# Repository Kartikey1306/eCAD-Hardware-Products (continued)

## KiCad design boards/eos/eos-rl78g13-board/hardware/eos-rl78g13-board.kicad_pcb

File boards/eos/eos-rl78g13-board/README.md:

# EoS RL78G13 Board

An original R5F100LEAFB RL78/G13 development board, 30 × 100 mm, two layers, with two
30-pin expansion headers, a USB-C serial port and an external TOOL0 debug connector.
Designed by Kartikeydheer Srivastava.
All rights reserved: not open source, and not under this repository's MIT licence.
Anyone may view it, clone this repository and run its tests; anything more needs
Kartikeydheer Srivastava's written permission (kartikeydheer@gmail.com). EmbeddedOS (EoS) Research Foundation has a limited, revocable
permission. See [LICENSE.txt](LICENSE.txt) and [the licence summary](../README.md#licence).

A board for the same job as the Renesas YRPBRL78G13; an original design, not a copy:
no design file of the vendor's was used; the header positions come from the 25.4 mm
separation and 30 × 100 mm envelope dimension callouts in
[Renesas R01UH0243ED0000 Rev.1.0, page 70](https://www.renesas.com/en/document/mah/rl78g13-stick-yrpbrl78g13),
with the 2.54 mm pitch and pin functions from pages 18–20. The undimensioned distance
along the board is an original choice: both pin-1 centres are 2.54 mm from the bottom edge.
No schematic, copper layout, Gerber or BOM from that board was used. Mechanical drop-in
compatibility is unverified. This board uses 3.3 V I/O; VDD is not the reference board's 5 V.

| | |
|---|---|
|  |  |

## What is on it

| Block | Parts, settings and source |
|---|---|
| MCU | Renesas [R5F100LEAFB#10](https://www.renesas.com/en/products/rl78-g13/part-details/r5f100leafb-10), LFQFP-64, 64 KB code flash, 4 KB data flash, 4 KB RAM. Internal high-speed oscillator supports 32 MHz at this supply; select HS flash mode in firmware. [R01DS0131EJ0380](https://www.renesas.com/en/document/dst/rl78g13-data-sheet), §§1.1–1.3.11 and electrical characteristics. |
| MCU supply | VDD and EVDD0 share the nominal 3.283 V rail; VSS and EVSS0 share ground. Each supply has 100 nF; REGC has a specified 680 nF, 35 V, ±10% X7R 0805 capacitor to ground (C3; see capacitance budget below). Unused X1/X2 inputs have individual 10 kΩ pull-downs. [R01UH0146EJ0380](https://www.renesas.com/en/document/man/rl78g13-users-manual-hardware), §2.2, Table 2-3 and §23.1. |
| RTC subclock | NDK NX3215SA-32.768K-STD-MUA-14, 32.768 kHz, CL = 6 pF, ESR ≤70 kΩ, with two 7 pF C0G loads. This combination appears in the RL78 hardware manual's §5.7 resonator table (R01UH0146EJ0380, Resonator and Oscillator Constants). [NDK NX3215SA](https://www.ndk.com/images/products/catalog/c_NX3215SA_e.pdf). Start with normal oscillation mode; measure frequency and startup on hardware before using a lower-power setting. |
| USB-C | HRO TYPE-C-31-M-12, 5.1 kΩ on each CC pin ([USB Type-C specification](https://www.usb.org/usb-type-cr-cable-and-connector-specification), Rd), SP0503BAHTG common-anode TVS on D+, D− and VBUS. There are no data-line steering diodes to VBUS. USB layout and bridge values follow [CP2102N Rev.1.5, §§2.1–2.3](https://www.silabs.com/documents/public/data-sheets/cp2102n-datasheet.pdf). |
| Supply | Littelfuse 1206L050YR 500 mA fuse, Nexperia PMEG6010CEH Schottky, TPS7A9101DSKR LDO. 3.57 kΩ / 1.15 kΩ, both 0.1%, set 3.283 V; 10 µF input, 10 µF output, 10 nF NR/SS. [TI TPS7A91 SBVS282A](https://www.ti.com/lit/ds/symlink/tps7a91.pdf), Table 7-1 and §7.1.3. |
| USB UART | CP2102N-A02-GQFN24R: TXD → P14/RxD2, RXD ← P13/TxD2. VIO, VDD and VREGIN share the board supply, each with 4.7 µF and 100 nF bypass. RSTb has 1 kΩ pull-up. VBUS sense uses 22.1 kΩ / 47.5 kΩ, plus 1.5 kΩ VBUS bleed. CP2102N Rev.1.5 Figs.2.3/2.5. |
| Debug | Unshrouded, unkeyed 2×7, 2.54 mm connector with the Renesas E1/E2/E2 Lite TOOL0 pinout (see the keying warning below); 1 kΩ TOOL0 pull-up, a reset-choice jumper (Fig.2-10) and a 10 kΩ RESET pull-up (Fig.2-11 asks 1–10 kΩ where RESET_OUT alone drives RESET). [R20UT1994, Table 2-2 and Figs.2-5, 2-10 and 2-11](https://www.renesas.com/en/document/mat/e1e20e2-emulator-e2-emulator-lite-additional-document-users-manual-notes-connection-rl78). |
| User I/O | Reset switch, P137/INTP0 user switch with 10 kΩ pull-up, red P17 LED with 750 Ω and yellow P16 LED with 680 Ω. Both LEDs are active high and share their expansion pins. [Kingbright red](https://www.kingbrightusa.com/images/catalog/SPEC/APTD1608LSURCK.pdf), [yellow](https://www.kingbrightusa.com/images/catalog/SPEC/APTD1608LSYCK.pdf) and [green power LED](https://www.kingbrightusa.com/images/catalog/SPEC/APTD1608LCGCK.pdf) specify typical VF at 2 mA. |

C3 is **Murata GCM21BR7YA684KA55L**, 680 nF, 35 V, ±10%, X7R, 0805.
The RL78 hardware manual §23.1/Table 23-1 requires 0.47–1 µF on REGC, whose
operating voltage is 1.8 or 2.1 V. [Murata electrical characteristic data](https://ds.murata.com/simserve/characteristics?ReqType=TechPDF&partnumber=GCM21BR7YA684KA55&lang=en&techpdfname=technical_pdf_Capacitor01)
and [SimSurfing](https://ds.murata.com/simsurfing/mlcc.html?partnumbers=%5B%22GCM21BR7YA684KA55%22%5D)
provide the part's bias and temperature models. A model sweep at 0.01 Vrms, −40 to
+85 °C in 5 °C steps, and 0–3.325 V gave 0.652–0.691 µF; DC-bias change relative
to zero bias stayed within ±0.74%. With the full ±10% tolerance and ±15% X7R
limits, a separate 3% bias/AC allowance and 5% aging reserve give a calculated
0.479–0.886 µF envelope. These allowances are design reserves, not manufacturer
guarantees: the models are typical. Qualify production lots and substitutions at
REGC voltage and temperature, including aging, against the 0.47–1 µF requirement.
C3 is placed next to REGC with a short ground return.

## Power and operation

Power the board through USB-C only. J1.2 and J2.2 are **3.3 V outputs**. Do not inject
power there or enable target power from an attached debug probe. The MCU and USB bridge
always share a rail, so a powered MCU cannot drive an unpowered bridge. The Schottky and
VBUS bleed also keep the sense input from reporting a host through leakage.

External loads on J1.2 and J2.2 share one **150 mA** budget. Reserve 40 mA for the board,
for a total below 190 mA. The board itself takes about 31 mA from data-sheet typical and
maximum values: MCU IDD1 ≤ 7.0 mA (R01DS0131), CP2102N 9.5 mA typical, the three LEDs
6.2 mA, the feedback divider 0.70 mA and the P137 button 0.33 mA on 3.3 V, plus the LDO's
ground current ≤ 3.5 mA and the 3.33 mA VBUS bleed on 5 V. **With an E1, E2 or E2 Lite
fitted**, the probe draws about 20 mA from VDD at 3.3 V (R20UT1994 §2.5.4) and a low TOOL0
adds 3.3 mA through R16: the board then needs about 54 mA, so keep external loads at or
below **130 mA** while a probe is connected. Before using that allowance, program the CP2102N Max Power
descriptor to 0xFA (500 mA), and let the USB host configure the device; its factory value
0x32 requests 100 mA (CP2102N Table 7.1). With the factory descriptor, or before USB
configuration, keep external loads at or below 50 mA. This is a design budget, not a
measured load limit or USB certification.

The board does not implement CP2102N SUSPEND-controlled load switching or MCU suspend
firmware. The MCU, power LED and VBUS bleed remain powered when the host suspends.
**This board does not meet the USB 2.0 suspend current limit:** the VBUS bleed alone draws
5.0 V / 1.5 kΩ = 3.33 mA, above the 2.5 mA allowed. Changing Max Power alone does not make
this a compliant high-power USB device: attach current, enumeration and attach inrush are
unverified. The 10 µF LDO
input capacitor has positive tolerance, and downstream capacitors (about 35 µF on 3.3 V,
including the 10 µF at the header supply) also charge during startup; the fuse and Schottky are not an active inrush limiter. Validate these cases
on a prototype and add load/inrush control before claiming USB power compliance.

At 190 mA, a 4.75 V source, fuse R1max = 0.70 Ω, and conservative diode drop 0.53 V leave
at least 4.087 V at the LDO. Its specified maximum dropout is 0.20 V at 1 A. Ignoring the
upstream drops, worst-case dissipation is approximately `(5.25 − 3.283) × 0.190 = 0.374 W`.
The LDO's 62.5 °C/W JEDEC figure predicts about 24 °C rise; the thermal resistance of this
two-layer board has not been measured. Verify temperature and supply droop on a prototype.
The fuse's 0.42 A hold rating at 40 °C exceeds this budget. See the
[Littelfuse 1206L product data](https://www.littelfuse.com/~/media/files/littelfuse/technical%20resources/documents/product%20catalogs/littelfuse_polyfuse_pptcs.pdf)
and [Nexperia PMEG6010CEH](https://assets.nexperia.com/documents/data-sheet/PMEG6010CEH.pdf).

JP1 uses **one shunt**:

| Position | Operation |
|---|---|
| 1–2 | Normal run: reset switch and J2.19 connect to MCU RESET. |
| 2–3 | External probe: its RESET_OUT connects to MCU RESET; the switch and J2.19 feed the probe's RESET_IN. |

Connect the debug cable with both systems powered off, align its pin 1, select JP1 2–3,
and disable probe target power. After debugging, power off, unplug the cable and return
JP1 to 1–2. Hot plugging is unsupported because the reset capacitance used for that mode
would change the interface. R15, 10 kΩ, pulls MCU RESET up: R20UT1994 Figure 2-11 asks
for 1–10 kΩ where RESET_OUT alone drives RESET, as it does with JP1 at 2–3. It draws
0.33 mA while RESET is held low and also keeps RESET from floating while JP1 is open; it
does not replace the operating shunt. Order one 2.54 mm two-position jumper shunt with JP1.

**J4 is not keyed.** It is a plain 2×7 pin header, because a keyed 25.0 mm box header
(R20UT1994 Figure 2-4) does not fit across this board between J1 and J2. Check pin 1 every
time: it is the square pad at J4's lower left, marked "1" on the silkscreen. A cable plugged in the
wrong way round puts probe pin k on board pin 15 − k. The probe's RESET_OUT (13) then
lands on board ground (2), and its TOOL0 (5) and ground (2) both land on E2_RSTOUT (pins 10
and 13), so the probe's TOOL0 is tied to its own ground. R20UT1994 §2.2 warns that a
cable connected the wrong way may be damaged. With J1 and J2 fitted on the top side, the
free span between their 2.54 mm housings is about 22.86 mm. A 14-way IDC socket is about
22.4 mm long (distributor data for 3M 89114-0101, not a 3M drawing), about 0.2 mm clear on
each side. The fit of the E2 Lite cable's own plug has not been checked.

| J4 pin | Signal | J4 pin | Signal |
|---|---|---|---|
| 1 | NC | 2 | GND |
| 3 | NC | 4 | NC |
| 5 | TOOL0 | 6 | RESET_IN |
| 7 | NC | 8 | VDD sense |
| 9 | TOOL0 supply sense | 10 | RESET_OUT |
| 11 | NC | 12 | GND |
| 13 | RESET_OUT | 14 | GND |

USB carries UART2, not native MCU USB. Configure P13 as TxD2 and P14 as RxD2. Do not drive
P14 from expansion hardware while the bridge is fitted: it is already driven by CP2102N
TXD. P11/P12 remain expansion GPIO/UART0. The board has no COM-port programming/debug
support; use J4 for programming. Firmware must configure unused expansion GPIO inputs
with pull-ups or as safe outputs to prevent floating inputs.

## Expansion pinout

With USB at the top, J1 is the right row and J2 the left row. Both are fitted on the top
side, with the components. Pin 1 is at the bottom, marked by a square pad, and numbering
proceeds toward USB. Rows are 25.4 mm apart.
The published signal assignment is retained; VDD is 3.3 V on this design.

| Pin | J1 | J2 |
|---|---|---|
| 1 | GND | GND |
| 2 | VDD output | VDD output |
| 3 | P10 | P140 |
| 4 | P11 | P141 |
| 5 | P12 | P00 |
| 6 | P13 / UART TX | P01 |
| 7 | P14 / UART RX | P02 |
| 8 | P15 | P03 |
| 9 | P16 / yellow LED | P04 |
| 10 | P17 / red LED | P130 (output only) |
| 11 | P55 | P20 / AVREFP |
| 12 | P54 | P21 / AVREFM |
| 13 | P53 | P22 |
| 14 | P52 | P23 |
| 15 | P51 | P24 |
| 16 | P50 | P25 |
| 17 | P60 / SCLA0 | P26 |
| 18 | P61 / SDAA0 | P27 |
| 19 | P62 | User reset |
| 20 | P63 | P120 |
| 21 | P31 | P43 |
| 22 | P77 | P42 |
| 23 | P76 | P41 |
| 24 | P75 | P137 / button (input only) |
| 25 | P74 | P146 |
| 26 | P73 | P147 |
| 27 | P72 | P06 |
| 28 | P71 | P05 |
| 29 | P70 | P30 |
| 30 | NC | NC |

P60–P63 are open-drain ports; supply suitable external pull-ups when using them as outputs.
Use 3.3 V peripherals and check the MCU's pin-specific limits. P20/P21 can be ADC reference
inputs; firmware must choose the intended ADC reference before use.

## Not on this board

- The vendor's proprietary on-board debug probe, its firmware, demonstration software and
  virtual-UART implementation. Standard TOOL0 and CP2102N replace those functions.
- A 5 V MCU supply, USB Mini-B, an MCU-only current-measurement jumper or an external
  supply input. All powered logic shares the regulated rail.
- A main-clock crystal. The internal high-speed oscillator supplies the CPU clock; the
  fitted 32.768 kHz crystal supplies the subsystem clock.
- The vendor's 9 mm USB-end corner radii. The original outline retains the 30 × 100 mm
  envelope with 1 mm corners; no enclosure-fit claim is made.

## Layout

The figures below were measured on the routed board with the independent review's scripts:
copper paths run through pads, tracks, vias and both pours on a 0.05 mm grid, and the
resistances assume 35 µm copper.

**3.3 V distribution.** The LDO's output capacitor C14 is the star point. Three branches leave
it, all laid as fixed routes before the autorouter runs:
- The headers and the debug connector: 85.1 mm down the free strip outside J2 to J2.2, then
  27.0 mm along the bottom edge through their own 10 µF + 100 nF (C22, C23) to J1.2. J4's VDD
  pins and the reset/TOOL0 pull-ups join this bus.
- The CP2102N: through the feedback divider's sense end (R8) to its bypass row, 9.0 mm.
- The MCU: from the same point through R11 and a trunk inside the MCU's right pad row to C1 and
  C2, 53.5 mm to VDD.

No header current passes the MCU's or the bridge's capacitors. With the MCU cluster's copper
removed the headers stay fed, and with the header feed removed the MCU stays fed. The nearest
3.3 V copper is 1.59 mm from the crystal and its load capacitors. The tracks stay 0.30 mm wide: a wider
track cannot enter the 0.5 mm-pitch pins of U1, U3 and U4, and the board generator gives every
track of a net the same width. At 150 mA the header feed drops about 21 mV at J2.2 (0.14 Ω) and
28 mV at J1.2 (0.18 Ω).

**Sub-clock crystal.** R01UH0146EJ0380 Figure 5-13(d) forbids a power or ground pattern under
the XT1/XT2 wiring and the resonator. Pour keep-outs leave both layers bare there: on each layer
the ground pour covers 0 % of the XT-line strip (x 13.9–15.1, y 50.4–55.0 mm) and of Y1's
footprint, and no via sits under the crystal. The load capacitors' ground loop (C4 to C5) joins
the MCU's ground at C2's ground pad by one route (Figure 5-13(f)). Router keep-outs on the loop's
other three sides stop the autorouter joining any other ground to it: with that one route cut,
the loop has no copper path to ground. The MCU's VSS/EVSS0 node reaches ground through the top
pour and C2's ground via, 0.81 mm from C2's pad, without using the loop. That is its only via:
there was no clear spot for one beside C1.

**CP2102N bypass.** Each capacitor's ground reaches the bridge's ground through a via into the
solid bottom pour:

| Capacitor | Copper path to U3.2 (GND) | To U3's exposed pad | Straight line to U3.2 |
|---|---|---|---|
| C21 100 nF | 5.06 mm | 5.12 mm | 3.86 mm |
| C17 100 nF | 5.55 mm | 5.60 mm | 4.81 mm |
| C19 100 nF | 6.50 mm | 6.55 mm | 5.75 mm |
| C16 4.7 µF | 7.75 mm | 7.80 mm | 7.05 mm |
| C18 4.7 µF | 9.30 mm | 9.35 mm | 8.59 mm |
| C20 4.7 µF | 10.85 mm | 10.90 mm | 10.13 mm |

C21, C17, C18 and C20 have their own via, 0.81–0.97 mm from the ground pad. C19 and C16 reach
their neighbours' vias through short top-layer tracks: the autorouter moved the vias placed for
them. Most of each path is the straight-line distance, so only re-placing the row could bring it
under 5 mm. The row stays west of the chip because the supply pins (5–7) are at its top-left
corner, the USB lines leave its top edge and the VBUS-sense and reset lines leave its left edge.

**TOOL0.** TOOL0 runs 43.6 mm on the top layer with no via. Its only long neighbour within 1 mm
is the 3.3 V feed of its own pull-up (23.2 mm), a DC rail. RESET runs 4.4 mm beside it where both
leave the MCU's pins, a slow line; the other runs are 1.9 mm or less, at the MCU's pins and just
below JP1. It no longer runs beside P04/SCK10 (R20UT1994 §2.5.2).

**USB connector.** The ESD array's common anode (U2.1) has its own ground via 1.0 mm away. Its
copper path is 7.14 mm to the receptacle's A1 ground contact and 12.69 mm to B1. VBUS still
crosses under the A-row D+ and D− on the bottom layer at y = 8.44 mm, at right angles: joining
the receptacle's two VBUS contact groups has to cross the pair somewhere. Full-speed USB should
tolerate a short crossing; its effect has not been measured.

**LDO.** The input capacitor C13 has a ground via 1.22 mm from its ground pad, with 8.98 mm of
copper to U4's thermal pad. C15 (NR/SS) has a via 0.78 mm from its ground pad. The TPS7A91's
1.2 × 2.0 mm thermal pad has **no vias**, although TI SBVS282A §7.4.1 asks for an array of
them. The board generator puts vias only in exposed pads over 1.5 mm across, and no spot beside
U4's ground pins was clear of other copper. Its heat spreads through the top pour; the nearest
ground via is 2.63 mm from the pad's centre. Measure the regulator's temperature on a prototype
before relying on the 0.374 W case above.

## Build results

The numbers below are from `build-report.json` and `drc.json` in this folder.

| Check | Result |
|---|---|
| Schematic ERC | 0 violations |
| DRC errors | 0 |
| Unconnected items | 0 |
| Schematic ↔ board parity | 0 differences |
| DRC warnings | 2: silkscreen within the board-edge clearance, the outline of J3 (USB-C), which sits at the board edge |

## Fabrication

Two layers, 1.6 mm FR-4, ground pours on both sides. Design rules use 0.15 mm clearance,
0.15 mm default signal tracks, 0.20 mm USB tracks, 0.25 mm ground tracks, 0.30 mm
regulated-supply tracks and 0.40 mm VBUS tracks; allowed minimum track width is 0.10 mm.
VBUS narrows to 0.30 mm for its last 0.9 mm into R7's 0402 pad, and +5V to 0.225 mm for
0.41 mm at C13; both carry under 0.2 A. Standard vias are 0.60 mm
with 0.30 mm drill, with a 0.25 mm minimum drill rule. The four vias in the CP2102N's
exposed pad (U3) sit inside its paste apertures, where tenting cannot cover them: order them
**filled and capped (IPC-4761 Type VII)**, so solder does not wick down them. The board
file asks for tenting only (plugging, filling and capping are "no"), so name this in the
fabrication order. Confirm
the fabrication files and actual minimum features before ordering.

## What has not been done

- **No board has been fabricated or tested.** Digital rule checks do not establish analog,
  USB, thermal, ESD, debug or crystal performance.
- No firmware, CP2102N configuration image, USB certification or hardware debug session
  is included. The Max Power descriptor change above is a setup requirement.
- The public drawing does not dimension the longitudinal header offset. Exact mechanical
  interchangeability, enclosure fit and cable clearance are unverified.

## Rebuild

```sh
python3 tools/eos_boards/build.py eos_rl78g13_board
```

The source is [tools/eos_boards/boards/eos_rl78g13_board.py](../../../tools/eos_boards/boards/eos_rl78g13_board.py).

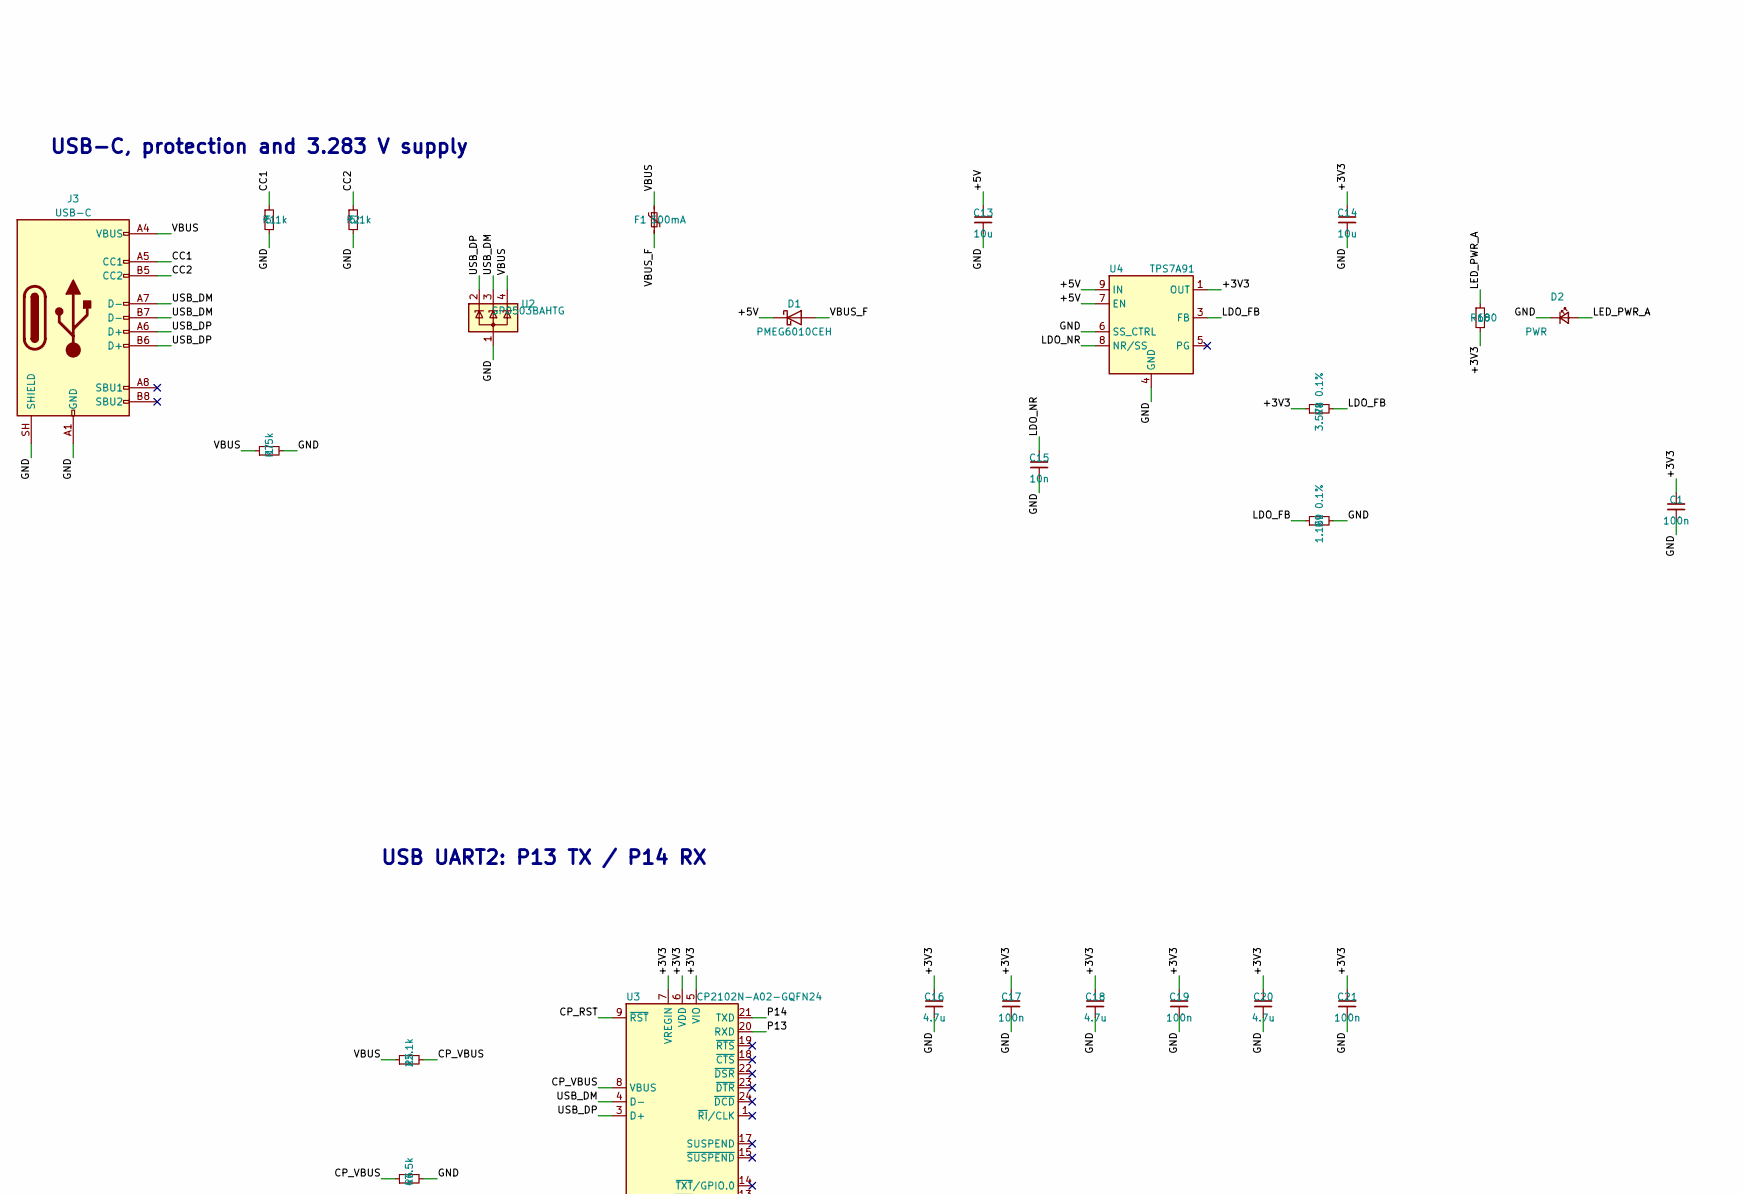
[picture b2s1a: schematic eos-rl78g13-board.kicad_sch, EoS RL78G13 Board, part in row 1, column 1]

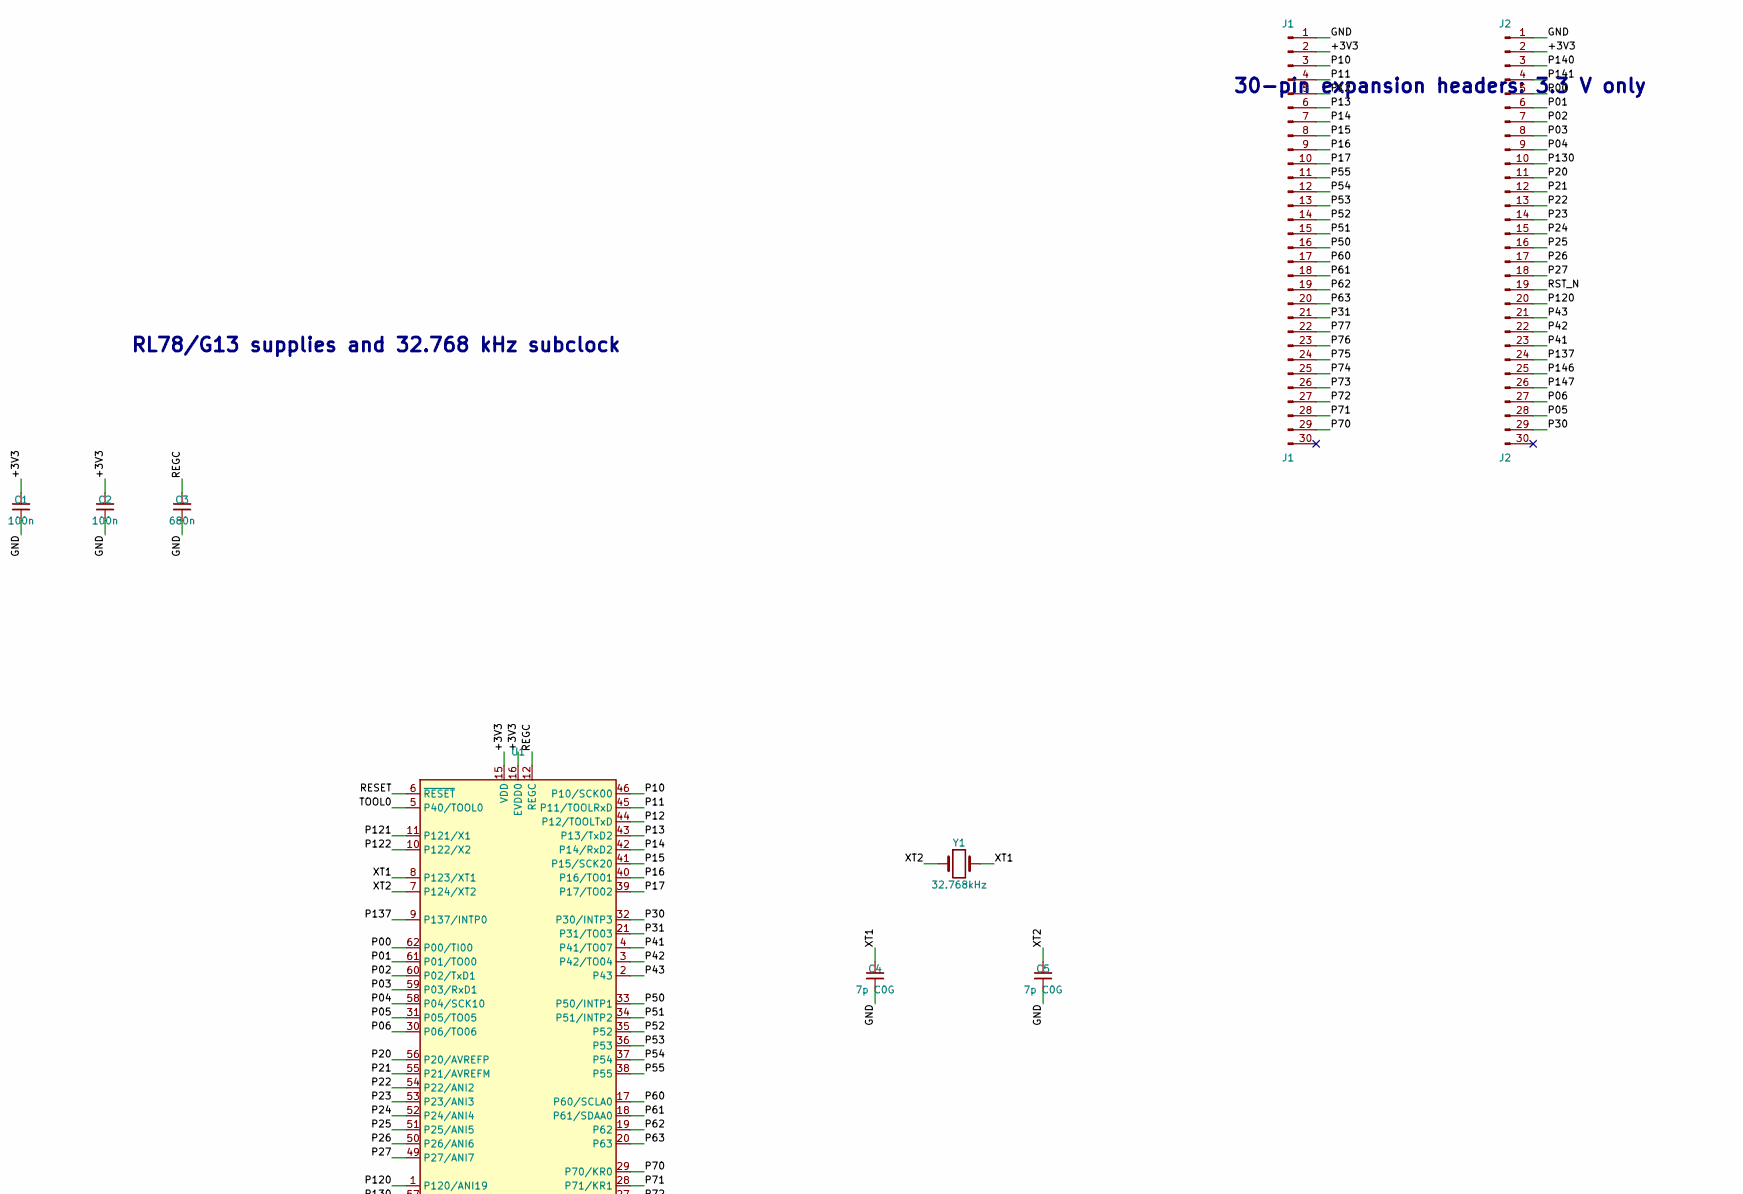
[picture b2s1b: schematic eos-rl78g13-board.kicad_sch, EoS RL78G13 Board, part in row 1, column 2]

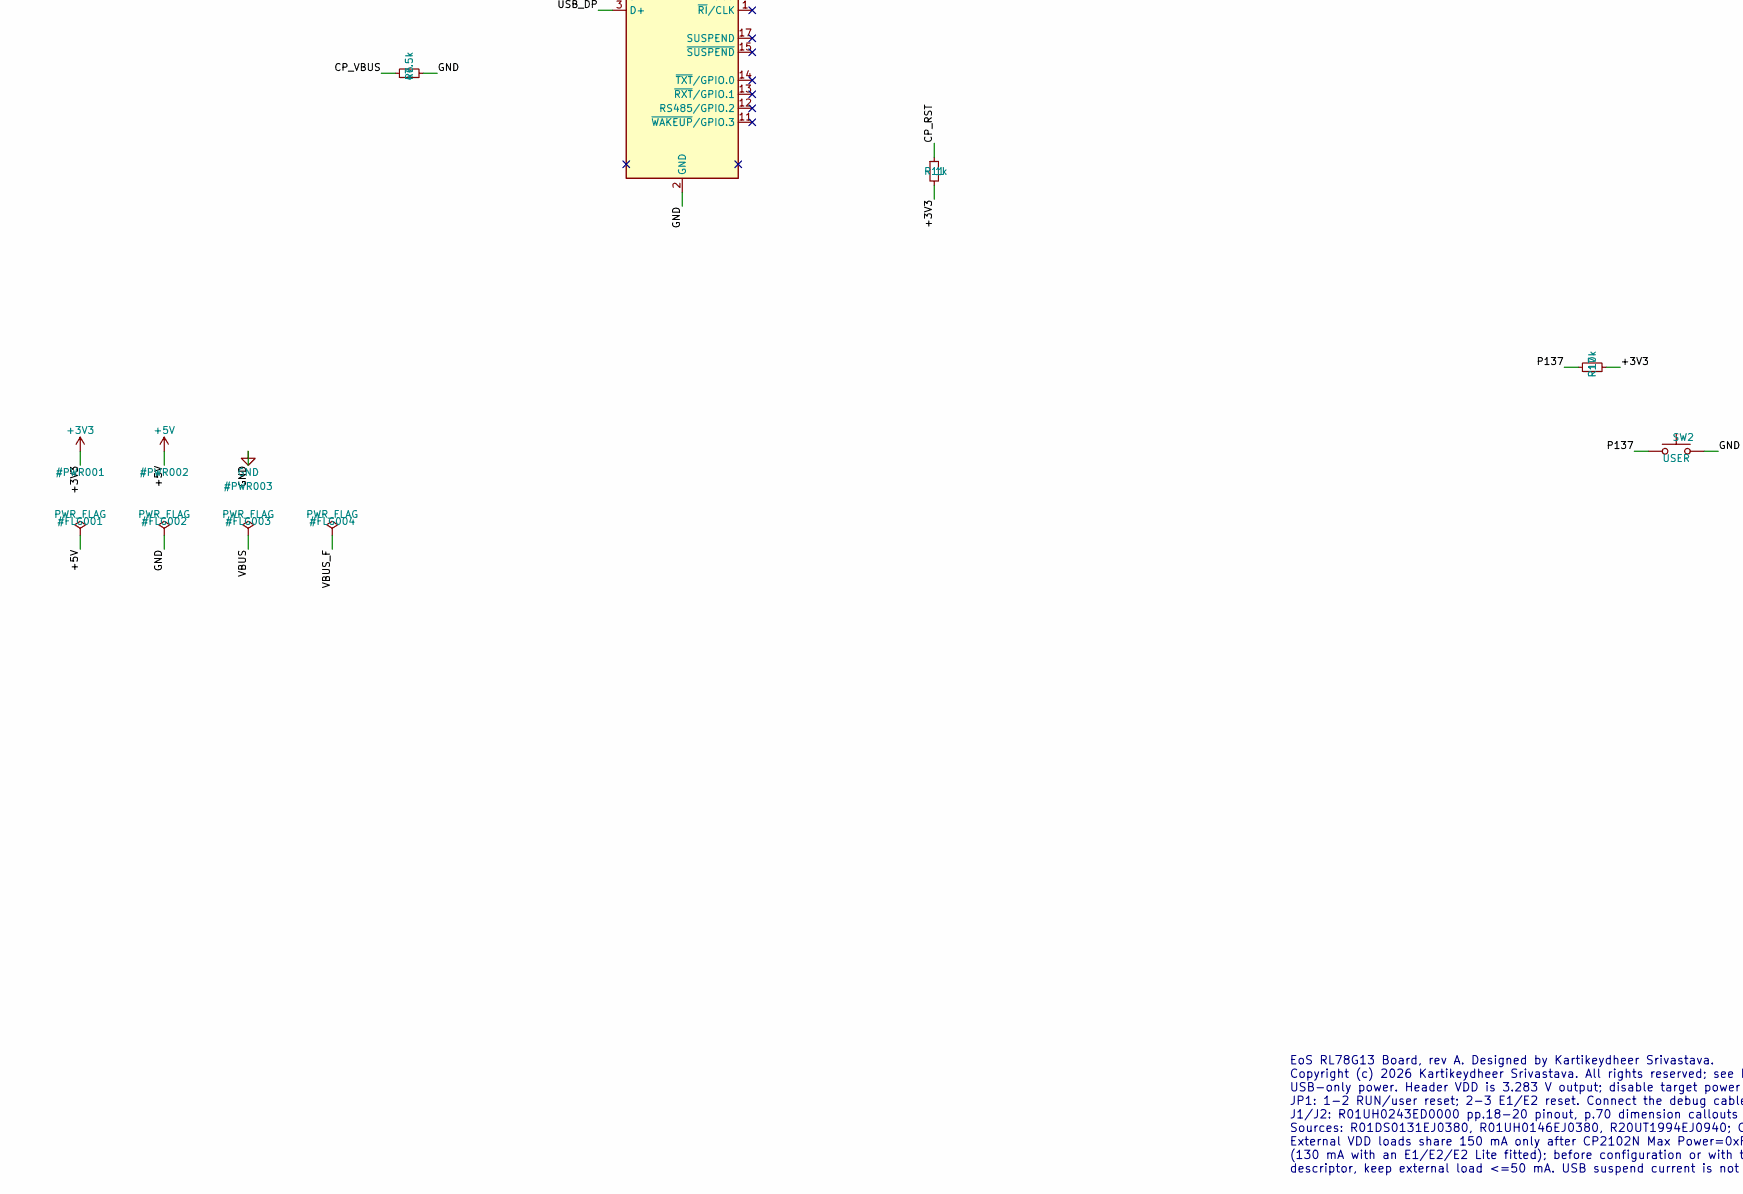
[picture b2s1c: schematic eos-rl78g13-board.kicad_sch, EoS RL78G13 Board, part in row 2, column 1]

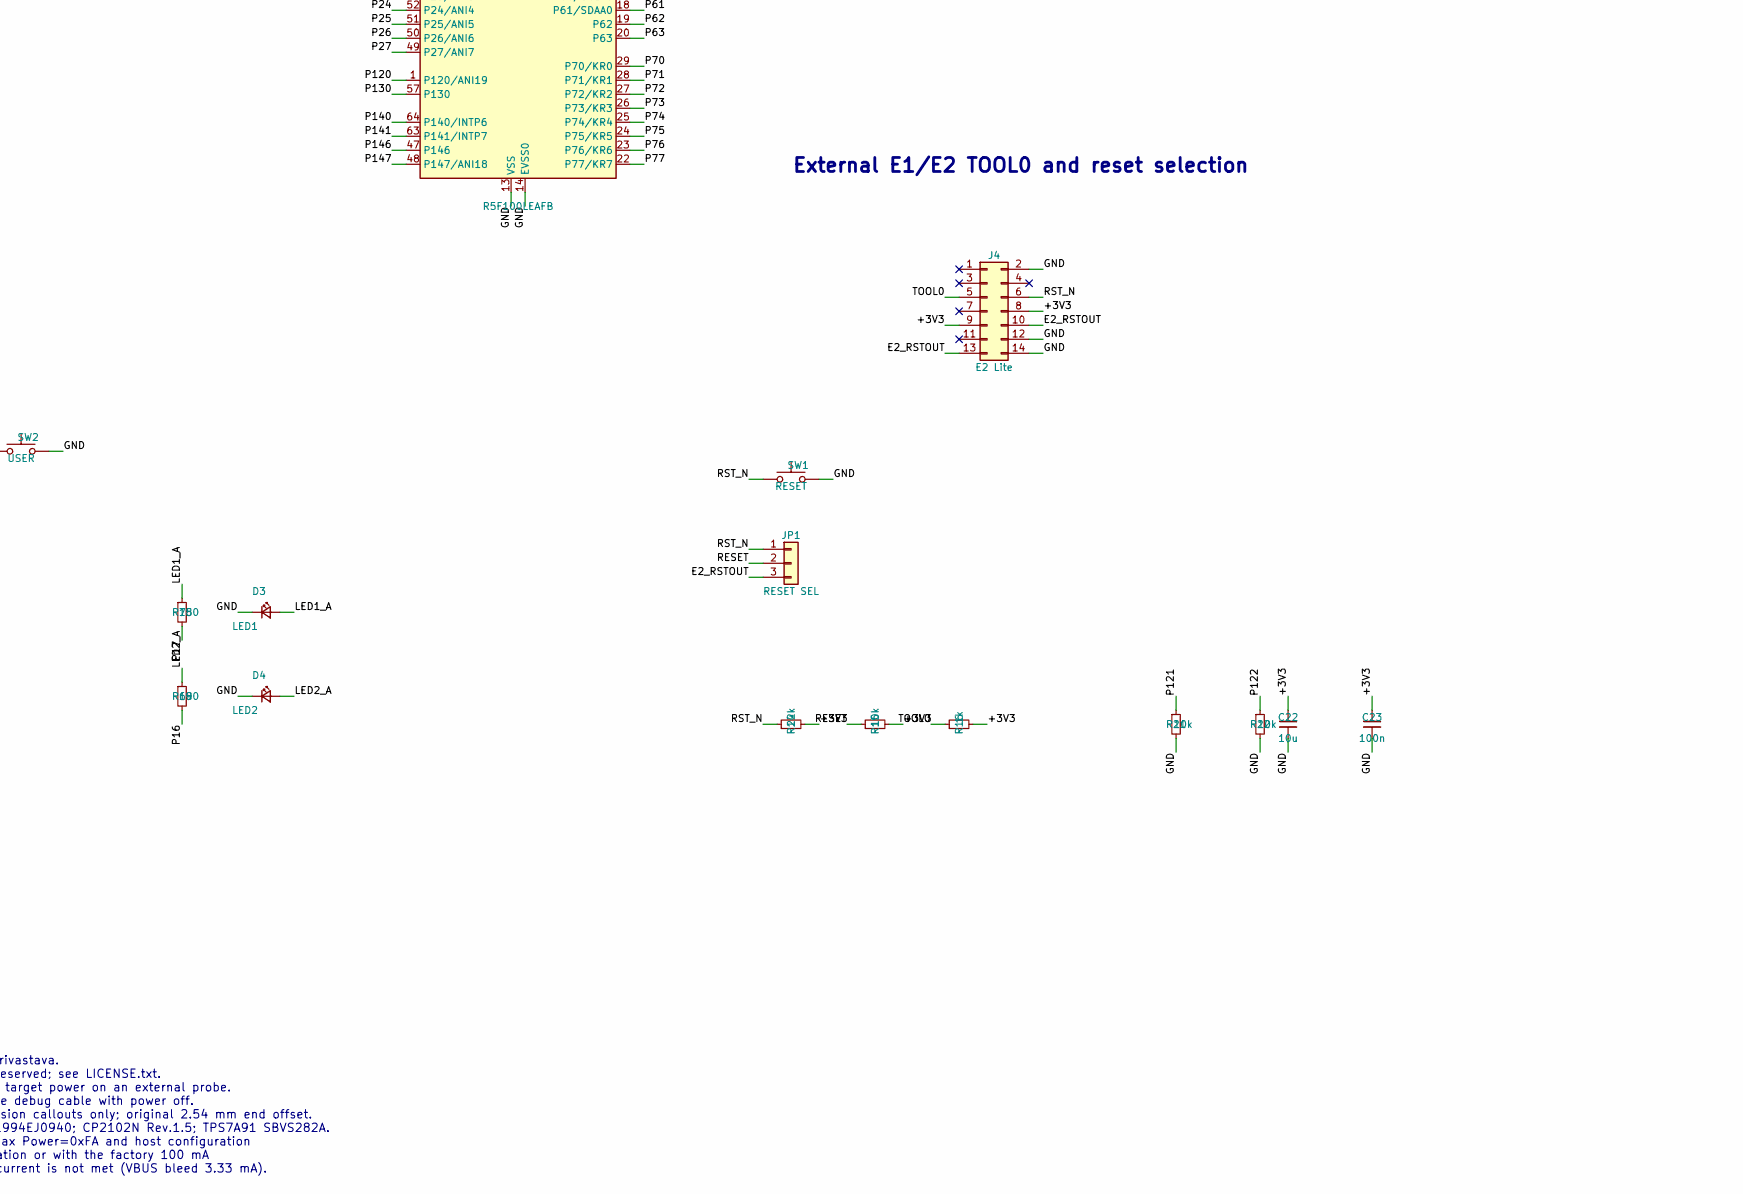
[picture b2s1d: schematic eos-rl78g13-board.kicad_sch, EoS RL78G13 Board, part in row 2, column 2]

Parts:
C1, C2, C17, C19, C21, C23: 100n; C_0402_1005Metric
C3: 680n; C_0805_2012Metric; MPN GCM21BR7YA684KA55L
C4, C5: 7p C0G; C_0402_1005Metric
C13, C14, C22: 10u; C_0805_2012Metric
C15: 10n; C_0402_1005Metric
C16, C18, C20: 4.7u; C_0603_1608Metric
D1: PMEG6010CEH; D_SOD-123F; MPN PMEG6010CEH,115
D2: PWR; LED_0603_1608Metric; MPN APTD1608LCGCK
D3: LED1; LED_0603_1608Metric; MPN APTD1608LSURCK
D4: LED2; LED_0603_1608Metric; MPN APTD1608LSYCK
F1: 500mA; Fuse_1206_3216Metric; MPN 1206L050YR
J1: J1; PinHeader_1x30_P2.54mm_Vertical
J2: J2; PinHeader_1x30_P2.54mm_Vertical
J3: USB-C; USB_C_Receptacle_HRO_TYPE-C-31-M-12; MPN TYPE-C-31-M-12
J4: E2 Lite; PinHeader_2x07_P2.54mm_Vertical
JP1: RESET SEL; PinHeader_1x03_P2.54mm_Vertical
R1, R2: 5.1k; R_0402_1005Metric
R5: 22.1k; R_0402_1005Metric
R6: 47.5k; R_0402_1005Metric
R7: 1.5k; R_0402_1005Metric
R8: 3.57k 0.1%; R_0402_1005Metric
R9: 1.15k 0.1%; R_0402_1005Metric
R10, R19: 680; R_0402_1005Metric
R11, R16: 1k; R_0402_1005Metric
R14: 22k; R_0402_1005Metric
R15, R17, R21, R22: 10k; R_0402_1005Metric
R18: 750; R_0402_1005Metric
SW1: RESET; SW_Push_1P1T_NO_CK_KMR2; MPN KMR221GLFS
SW2: USER; SW_Push_1P1T_NO_CK_KMR2; MPN KMR221GLFS
U1: R5F100LEAFB; LQFP-64_10x10mm_P0.5mm; MPN R5F100LEAFB#10
U2: SP0503BAHTG; SOT-143; MPN SP0503BAHTG
U3: CP2102N-A02-GQFN24; QFN-24-1EP_4x4mm_P0.5mm_EP2.6x2.6mm; MPN CP2102N-A02-GQFN24R
U4: TPS7A91; Texas_S-PDSO-N10_EP1.2x2mm; MPN TPS7A9101DSKR
Y1: 32.768kHz; Crystal_SMD_3215-2Pin_3.2x1.5mm; MPN NX3215SA-32.768K-STD-MUA-14

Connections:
+3V3: C1.1, C2.1, C14.1, C16.1, C17.1, C18.1, C19.1, C20.1, C21.1, C22.1, C23.1, J1.2, J2.2, J4.8, J4.9, R8.1, R10.2, R11.2, R14.2, R15.2, R16.2, R17.2, U1.15 (VDD), U1.16 (EVDD0), U3.5 (VIO), U3.6 (VDD), U3.7 (VREGIN), U4.1 (OUT), U4.2 (OUT)
+5V: C13.1, D1.1 (K), U4.7 (EN), U4.9 (IN), U4.10 (IN)
/CC1: J3.A5 (CC1), R1.1
/CC2: J3.B5 (CC2), R2.1
/CP_RST: R11.1, U3.9 (~RST)
/CP_VBUS: R5.2, R6.1, U3.8 (VBUS)
/E2_RSTOUT: J4.10, J4.13, JP1.3
/LDO_FB: R8.2, R9.1, U4.3 (FB)
/LDO_NR: C15.1, U4.8 (NR/SS)
/LED1_A: D3.2 (A), R18.1
/LED2_A: D4.2 (A), R19.1
/LED_PWR_A: D2.2 (A), R10.1
/P00: J2.5, U1.62 (P00/TI00)
/P01: J2.6, U1.61 (P01/TO00)
/P02: J2.7, U1.60 (P02/TxD1)
/P03: J2.8, U1.59 (P03/RxD1)
/P04: J2.9, U1.58 (P04/SCK10)
/P05: J2.28, U1.31 (P05/TO05)
/P06: J2.27, U1.30 (P06/TO06)
/P10: J1.3, U1.46 (P10/SCK00)
/P11: J1.4, U1.45 (P11/TOOLRxD)
/P12: J1.5, U1.44 (P12/TOOLTxD)
/P13: J1.6, U1.43 (P13/TxD2), U3.20 (RXD)
/P14: J1.7, U1.42 (P14/RxD2), U3.21 (TXD)
/P15: J1.8, U1.41 (P15/SCK20)
/P16: J1.9, R19.2, U1.40 (P16/TO01)
/P17: J1.10, R18.2, U1.39 (P17/TO02)
/P20: J2.11, U1.56 (P20/AVREFP)
/P21: J2.12, U1.55 (P21/AVREFM)
/P22: J2.13, U1.54 (P22/ANI2)
/P23: J2.14, U1.53 (P23/ANI3)
/P24: J2.15, U1.52 (P24/ANI4)
/P25: J2.16, U1.51 (P25/ANI5)
/P26: J2.17, U1.50 (P26/ANI6)
/P27: J2.18, U1.49 (P27/ANI7)
/P30: J2.29, U1.32 (P30/INTP3)
/P31: J1.21, U1.21 (P31/TO03)
/P41: J2.23, U1.4 (P41/TO07)
/P42: J2.22, U1.3 (P42/TO04)
/P43: J2.21, U1.2 (P43)
/P50: J1.16, U1.33 (P50/INTP1)
/P51: J1.15, U1.34 (P51/INTP2)
/P52: J1.14, U1.35 (P52)
/P53: J1.13, U1.36 (P53)
/P54: J1.12, U1.37 (P54)
/P55: J1.11, U1.38 (P55)
/P60: J1.17, U1.17 (P60/SCLA0)
/P61: J1.18, U1.18 (P61/SDAA0)
/P62: J1.19, U1.19 (P62)
/P63: J1.20, U1.20 (P63)
/P70: J1.29, U1.29 (P70/KR0)
/P71: J1.28, U1.28 (P71/KR1)
/P72: J1.27, U1.27 (P72/KR2)
/P73: J1.26, U1.26 (P73/KR3)
/P74: J1.25, U1.25 (P74/KR4)
/P75: J1.24, U1.24 (P75/KR5)
/P76: J1.23, U1.23 (P76/KR6)
/P77: J1.22, U1.22 (P77/KR7)
/P120: J2.20, U1.1 (P120/ANI19)
/P121: R21.1, U1.11 (P121/X1)
/P122: R22.1, U1.10 (P122/X2)
/P130: J2.10, U1.57 (P130)
/P137: J2.24, R17.1, SW2.1, U1.9 (P137/INTP0)
/P140: J2.3, U1.64 (P140/INTP6)
/P141: J2.4, U1.63 (P141/INTP7)
/P146: J2.25, U1.47 (P146)
/P147: J2.26, U1.48 (P147/ANI18)
/REGC: C3.1, U1.12 (REGC)
/RESET: JP1.2, R15.1, U1.6 (~RESET)
/RST_N: J2.19, J4.6, JP1.1, R14.1, SW1.1
/TOOL0: J4.5, R16.1, U1.5 (P40/TOOL0)
/USB_DM: J3.A7 (D-), J3.B7 (D-), U2.3 (K), U3.4 (D-)
/USB_DP: J3.A6 (D+), J3.B6 (D+), U2.2 (K), U3.3 (D+)
/VBUS: F1.1, J3.A4 (VBUS), J3.A9 (VBUS), J3.B4 (VBUS), J3.B9 (VBUS), R5.1, R7.1, U2.4 (K)
/VBUS_F: D1.2 (A), F1.2
/XT1: C4.1, U1.8 (P123/XT1), Y1.2
/XT2: C5.1, U1.7 (P124/XT2), Y1.1
GND: C1.2, C2.2, C3.2, C4.2, C5.2, C13.2, C14.2, C15.2, C16.2, C17.2, C18.2, C19.2, C20.2, C21.2, C22.2, C23.2, D2.1 (K), D3.1 (K), D4.1 (K), J1.1, J2.1, J3.A1 (GND), J3.A12 (GND), J3.B1 (GND), J3.B12 (GND), J3.SH (SHIELD), J4.2, J4.12, J4.14, R1.2, R2.2, R6.2, R7.2, R9.2, R21.2, R22.2, SW1.2, SW2.2, U1.13 (VSS), U1.14 (EVSS0), U2.1 (A), U3.2 (GND), U3.25 (GND), U4.4 (GND), U4.6 (SS_CTRL), U4.11 (GND)

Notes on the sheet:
USB-C, protection and 3.283 V supply
USB UART2: P13 TX / P14 RX
RL78/G13 supplies and 32.768 kHz subclock
External E1/E2 TOOL0 and reset selection
30-pin expansion headers: 3.3 V only
EoS RL78G13 Board, rev A. Designed by Kartikeydheer Srivastava. Copyright (c) 2026 Kartikeydheer Srivastava. All rights reserved; see LICENSE.txt. USB-only power. Header VDD is 3.283 V output; disable target power on an external probe. JP1: 1-2 RUN/user reset; 2-3 E1/E2 reset. Connect the debug cab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

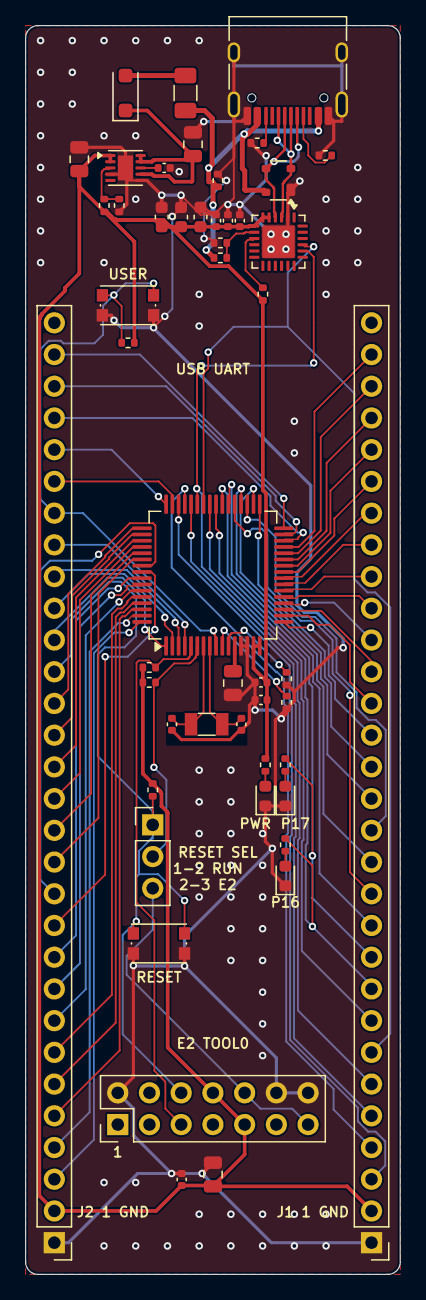
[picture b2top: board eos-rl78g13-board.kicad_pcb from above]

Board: 2 copper layers, 30.0 x 100.0 mm, 50 parts (0 on the bottom side), 78 nets.

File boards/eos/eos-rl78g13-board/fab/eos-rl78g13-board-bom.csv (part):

"Refs","Value","Footprint","Manufacturer","MPN","Description","Qty","DNP"
"C1,C2,C17,C19,C21,C23","100n","Capacitor_SMD:C_0402_1005Metric","","","Any vendor: 100 nF 10% 10 V X7R 0402; EVDD0 bypass, Renesas R01UH0146EJ0380 section 2.2 (0.1 uF shortest path to EVSS0),Any vendor: 100 nF 10% 10 V X7R 0402; Silicon Labs CP2102N Rev.1.5 Fig.2.3 VDD bypass,Any vendor: 100 nF 10% 10 V X7R 0402; Silicon Labs CP2102N Rev.1.5 Fig.2.3 VIO bypass,Any vendor: 100 nF 10% 10 V X7R 0402; Silicon Labs CP2102N Rev.1.5 Fig.2.3 VREGIN bypass,Any vendor: 100 nF 10% 10 V X7R 0402; VDD bypass, Renesas R01UH0146EJ0380 section 2.2 (0.1 uF shortest path to VSS),Any vendor: 100 nF 10% 10 V X7R 0402; header/debug VDD high-frequency bypass","6",""
"C3","680n","Capacitor_SMD:C_0805_2012Metric","Murata","GCM21BR7YA684KA55L","680 nF 35 V X7R 10% 0805 REGC bypass; RL78 R01UH0146EJ0380 section 23.1: 0.47-1 uF at 1.8/2.1 V; see README derating evidence","1",""
"C4,C5","7p C0G","Capacitor_SMD:C_0402_1005Metric","","","Any vendor: 7 pF +/-0.25 pF C0G (NP0) 50 V 0402; Renesas R01UH0146EJ0380 section 5.7 XT1 resonator table, NX3215SA CL=6 pF","2",""
"C13,C14,C22","10u","Capacitor_SMD:C_0805_2012Metric","","","Any vendor: 10 uF 10% 10 V X5R 0805; header/debug VDD bulk, TI TPS7A91 SBVS282A section 5.3 (COUT >= 10 uF, no maximum),Any vendor: 10 uF 10% 10 V X5R 0805; input capacitor, TI TPS7A91 SBVS282A section 7.1.3 (>=10 uF nominal, 50% derating included),Any vendor: 10 uF 10% 10 V X5R 0805; output capacitor, TI TPS7A91 SBVS282A section 7.1.3 (10 uF nominal, 50% derating included)","3",""
"C15","10n","Capacitor_SMD:C_0402_1005Metric","","","Any vendor: 10 nF 10% 16 V X7R 0402; noise reduction/soft-start, TI TPS7A91 SBVS282A section 7.1.2.2","1",""
"C16,C18,C20","4.7u","Capacitor_SMD:C_0603_1608Metric","","","Any vendor: 4.7 uF 10% 10 V X5R 0603; Silicon Labs CP2102N Rev.1.5 Fig.2.3 VDD bypass,Any vendor: 4.7 uF 10% 10 V X5R 0603; Silicon Labs CP2102N Rev.1.5 Fig.2.3 VIO bypass,Any vendor: 4.7 uF 10% 10 V X5R 0603; Silicon Labs CP2102N Rev.1.5 Fig.2.3 VREGIN bypass","3",""
"D1","PMEG6010CEH","Diode_SMD:D_SOD-123F","Nexperia","PMEG6010CEH,115","PMEG6010CEH v.4: 60 V 1 A Schottky, VF <=0.53 V at 0.5 A; USB reverse isolation","1",""
"D2","PWR","LED_SMD:LED_0603_1608Metric","Kingbright","APTD1608LCGCK","Kingbright APTD1608LCGCK low-current green LED, 1.9 V typical at 2 mA","1",""
"D3","LED1","LED_SMD:LED_0603_1608Metric","Kingbright","APTD1608LSURCK","Kingbright APTD1608LSURCK low-current red LED, 1.75 V typical at 2 mA; P17 active-high","1",""
"D4","LED2","LED_SMD:LED_0603_1608Metric","Kingbright","APTD1608LSYCK","Kingbright APTD1608LSYCK low-current yellow LED, 1.85 V typical at 2 mA; P16 active-high","1",""
"F1","500mA","Fuse:Fuse_1206_3216Metric","Littelfuse","1206L050YR","1206L series: 0.50 A hold, 1.00 A trip, 6 V; R1max 0.70 ohm; derates to 0.42 A at 40 C","1",""
"J1","J1","Connector_PinHeader_2.54mm:PinHeader_1x30_P2.54mm_Vertical","","","Any vendor: 1x30 2.54 mm male pin header, vertical through-hole, gold, fitted on the top side; Renesas R01UH0243ED0000 Table 5 pinout, VDD=3.3 V output only, P13/P14 shared with USB UART","1",""
"J2","J2","Connector_PinHeader_2.54mm:PinHeader_1x30_P2.54mm_Vertical","","","Any vendor: 1x30 2.54 mm male pin header, vertical through-hole, gold, fitted on the top side; Renesas R01UH0243ED0000 Table 6 pinout, VDD=3.3 V output only","1",""
"J3","USB-C","Connector_USB:USB_C_Receptacle_HRO_TYPE-C-31-M-12","Korean Hroparts","TYPE-C-31-M-12","USB Type-C 5 V sink; HRO land pattern origin 3.19 mm from board edge","1",""
"J4","E2 Lite","Connector_PinHeader_2.54mm:PinHeader_2x07_P2.54mm_Vertical","","","Any vendor: 2x7 2.54 mm male pin header, vertical through-hole, gold, unshrouded and unkeyed (see README); Renesas E1/E2/E2 Lite pinout, R20UT1994EJ0940 Table 2-2; disable probe target-power output; connect with power off","1",""
"JP1","RESET SEL","Connector_PinHeader_2.54mm:PinHeader_1x03_P2.54mm_Vertical","","","Any vendor: 1x3 2.54 mm male pin header, vertical through-hole, gold; also order 1 x 2.54 mm two-position jumper shunt (1-2 user reset, 2-3 external probe); Renesas R20UT1994EJ0940 Fig.2-10","1",""
"R1,R2","5.1k","Resistor_SMD:R_0402_1005Metric","","","Any vendor: 5.1 kohm 1% 1/16 W 0402; USB Type-C Rev.2.4 Table 4-28: sink CC1 Rd,Any vendor: 5.1 kohm 1% 1/16 W 0402; USB Type-C Rev.2.4 Table 4-28: sink CC2 Rd","2",""
"R5","22.1k","Resistor_SMD:R_0402_1005Metric","","","Any vendor: 22.1 kohm 1% 1/16 W 0402; CP2102N VBUS divider upper (47.5 kohm lower), Silicon Labs CP2102N Rev.1.5 Fig.2.5","1",""
"R6","47.5k","Resistor_SMD:R_0402_1005Metric","","","Any vendor: 47.5 kohm 1% 1/16 W 0402; CP2102N VBUS divider lower (22.1 kohm upper), Silicon Labs CP2102N Rev.1.5 Fig.2.5","1",""
"R7","1.5k","Resistor_SMD:R_0402_1005Metric","","","Any vendor: 1.5 kohm 1% 1/16 W 0402 (16.7 mW at 5 V); VBUS bleed: with 69.6 kohm divider, 0.5 mA leakage gives 0.734 V; PMEG6010CEH reverse-leakage characteristic","1",""
"R8","3.57k 0.1%","Resistor_SMD:R_0402_1005Metric","","","Any vendor: 3.57 kohm 0.1% 25 ppm/C thin film 1/16 W 0402; feedback upper resistor, TI SBVS282A Table 7-1 gives 3.283 V with 1.15 kohm lower","1",""
"R9","1.15k 0.1%","Resistor_SMD:R_0402_1005Metric","","","Any vendor: 1.15 kohm 0.1% 25 ppm/C thin film 1/16 W 0402; feedback lower resistor, TI SBVS282A Table 7-1","1",""
"R10,R19","680","Resistor_SMD:R_0402_1005Metric","","","Any vendor: 680 ohm 1% 1/16 W 0402; (3.283-1.85)/680 = 2.11 mA nominal, Kingbright APTD1608LSYCK VF at 2 mA,Any vendor: 680 ohm 1% 1/16 W 0402; (3.283-1.9)/680 = 2.03 mA, Kingbright APTD1608LCGCK VF typical at 2 mA","2",""
"R11,R16","1k","Resistor_SMD:R_0402_1005Metric","","","Any vendor: 1 kohm 1% 1/16 W 0402; CP2102N RSTb pull-up, Silicon Labs CP2102N Rev.1.5 Fig.2.3,Any vendor: 1 kohm 1% 1/16 W 0402; TOOL0 pull-up, Renesas R20UT1994EJ0940 Fig.2-5","2",""
"R14","22k","Resistor_SMD:R_0402_1005Metric","","","Any vendor: 22 kohm 1% 1/16 W 0402; user-reset pull-up, R01DS0131EJ0380 DC leakage <=1 uA gives <=22 mV droop; shunt separates this from E2 RESET_OUT","1",""
"R15,R17,R21,R22","10k","Resistor_SMD:R_0402_1005Metric","","","Any vendor: 10 kohm 1% 1/16 W 0402; RESET pull-up, R20UT1994EJ0940 Fig.2-11 asks 1-10 kohm where RESET_OUT alone drives RESET (JP1 2-3); 0.33 mA while held low,Any vendor: 10 kohm 1% 1/16 W 0402; input-only P137 pull-up, R01DS0131EJ0380 DC input leakage <=1 uA gives <=10 mV droop, held button draws 0.328 mA,Any vendor: 10 kohm 1% 1/16 W 0402; unused input-only P121: Renesas R01UH0146EJ0380 Table 2-3 requires resistor to VSS; 10 kohm limits 1 uA leakage to 10 mV,Any vendor: 10 kohm 1% 1/16 W 0402; unused input-only P122: Renesas R01UH0146EJ0380 Table 2-3 requires resistor to VSS; 10 kohm limits 1 uA leakage to 10 mV","4",""
"R18","750","Resistor_SMD:R_0402_1005Metric","","","Any vendor: 750 ohm 1% 1/16 W 0402; (3.283-1.75)/750 = 2.04 mA nominal, Kingbright APTD1608LSURCK VF at 2 mA","1",""
"SW1","RESET","Button_Switch_SMD:SW_Push_1P1T_NO_CK_KMR2","C&K","KMR221GLFS","C&K KMR221GLFS momentary reset switch, active low","1",""
"SW2","USER","Button_Switch_SMD:SW_Push_1P1T_NO_CK_KMR2","C&K","KMR221GLFS","C&K KMR221GLFS momentary user switch on input-only P137/INTP0","1",""
"U1","R5F100LEAFB","Package_QFP:LQFP-64_10x10mm_P0.5mm","Renesas","R5F100LEAFB#10","RL78/G13 64 KB code flash, 4 KB data flash, 4 KB RAM, LFQFP-64; R01DS0131EJ0380 sections 1.1-1.3.11","1",""
"U2","SP0503BAHTG","Package_TO_SOT_SMD:SOT-143","Littelfuse","SP0503BAHTG","SP05xxBA datasheet: 5.5 V common-anode TVS, 30 pF typ; CP2102N Rev.1.5 Fig.2.5","1",""
"U3","CP2102N-A02-GQFN24","Package_DFN_QFN:QFN-24-1EP_4x4mm_P0.5mm_EP2.6x2.6mm","Silicon Labs","CP2102N-A02-GQFN24R","CP2102N Rev.1.5 Fig.2.3: VIO/VDD/VREGIN from board rail, internal regulator unused","1",""
"U4","TPS7A91","Package_DFN_QFN:Texas_S-PDSO-N10_EP1.2x2mm","Texas Instruments","TPS7A9101DSKR","TPS7A91 SBVS282A: 1 A adjustable LDO, nominal 3.283 V, 1% accuracy, thermal pad grounded","1",""
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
